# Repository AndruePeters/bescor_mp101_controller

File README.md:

# Bescor MP101 Controller

Solution to wirelessly control the Bescor MP101 pan and tilt camera motor.
User uses a PS4 controller to control the motor.

## Software Used
* [wiringPi](http://wiringpi.com/)
* [RF24](https://github.com/nRF24/RF24)
* [yaml-cpp](https://github.com/jbeder/yaml-cpp)
* [sfml](https://www.sfml-dev.org/)

## Devices Used
* [Arduino Uno](https://store.arduino.cc/usa/arduino-uno-rev3/) (although, I am using a cheap alternative from China.)
* [Raspberry Pi 3 Model B](https://www.raspberrypi.org/products/raspberry-pi-3-model-b/)
* [nRF24L01+ 2.4GHz](https://www.sparkfun.com/datasheets/Components/SMD/nRF24L01Pluss_Preliminary_Product_Specification_v1_0.pdf)
* [PS4 DualShock 4 Controller](https://www.playstation.com/en-us/explore/accessories/gaming-controllers/dualshock-4/)

# Installation

## Building
The following will actually compile and build the program natively on a Raspberry Pi. Please make sure that all dependencies are installed by running the install.sh script.

```
  (cd into the bescor_mp101_controller directory)
  cmake . -Bbuild
  cmake --build build
```

## Raspberry Pi
* **wiringPi** (dynamically linked since it is preinstalled)
  * wiringPi is installed by default. Follow [the instructions](http://wiringpi.com/download-and-install/) if you need to install it.
* **RF24** (statically linked)
  * `git clone https://github.com/nRF24/RF24`
  * `cd RF24/`
  * `./configure`
  * `sudo make install`
* **yaml-cpp** (statically inked)
  * Follow the instructions [here](https://github.com/jbeder/yaml-cpp).
* **sfml** (need to decide - probably statically linked)
  * If you have Debian then run `sudo apt-get install libsfml-dev`
  * Otherwise, follow the [official guide](https://www.sfml-dev.org/tutorials/2.5/start-linux.php) to manually install it. Version is 2.5 at the time of writing.

## YAML Configuration
Configuration settings for each node.
Example yaml file.
```yaml
camera_nodes:
  # this is the first came
  - channel: 1
    id: 1
    address: 1
    color: BLUE
    power_level: MAX
    data_rate: 250KBPS
    crc_length: DISABLED
    ir_proto: SONY
    zoom_in: 5
    zoom_out: 5
    focus_in: 5
    focus_out: 5

  # add following cameras here
```

#### Channel
Only channel 1 is supported at the moment

#### ID
Acceptable values: 1 - 255
0 is not allowed.

#### Address
Acceptable values: A1, A2, A3, A4, A5
At this point in time, I recommend only using A1

#### Color
Acceptable values:  OFF, BLUE, GREEN, CYAN, RED, MAGENTA, YELLOW, WHITE

#### Power Level
Acceptable values: MIN, LOW, HIGH, MAX

#### Data Rate
Acceptable values: 250KBPS, 1MBPS, 2MBPS
* The lower the speed the further the range. No reason in changing from 250KBPS for this application.

#### CRC Length
Acceptable values: DISABLED, CRC_8, CRC_16

#### IR Protocol
Acceptable values: SONY, NEC
* Hopefully, more will be supported in the future.

#### Zoom In, Zoom Out, Focus In, Focus Out
Any 32 bit number.

## Cross-compile
I created a basic [toolchain](https://github.com/AndruePeters/pi_toolchain) to cross compile for the Raspberry Pi.
The toolchain is simply the standard Raspberry Pi toolchain with precompiled libraries and headers I commonly use for my projects.
I'll write a better cross-compile description once I get the full thing back up.

# Controls
* L1 - cycles camera selection left
* R1 - cycles camera selection right
* L  - Controls the camera.
* R
  * Moving up and down zooms in and out
  * Moving left and right focuses in and out

# Packet Structure
## Motor Packets
`packet.packet_type = 0;`

`packet.payload_used = 3;`

`packet.payload[0] = speed`  This is an integer [0-255]

`packet.payload[1] = x_axis`. Values = {0, 1, 2}. 0 is off, 1 is left, 2 is right.

`packet.payloadp2] = y_axis`. Values = {0, 1, 2}. 0 is off, 1 is down, 2 is up.

## IR Packet
`packet.packet_type = 1;`

`packet.payload_used = 5;`

`packet.payload[0] = IR prot.`

`packet.payload[1 through 4]` is a 32 bit integer code with packet.payload[1] being the MSByte and packet.payload[4] LSByte

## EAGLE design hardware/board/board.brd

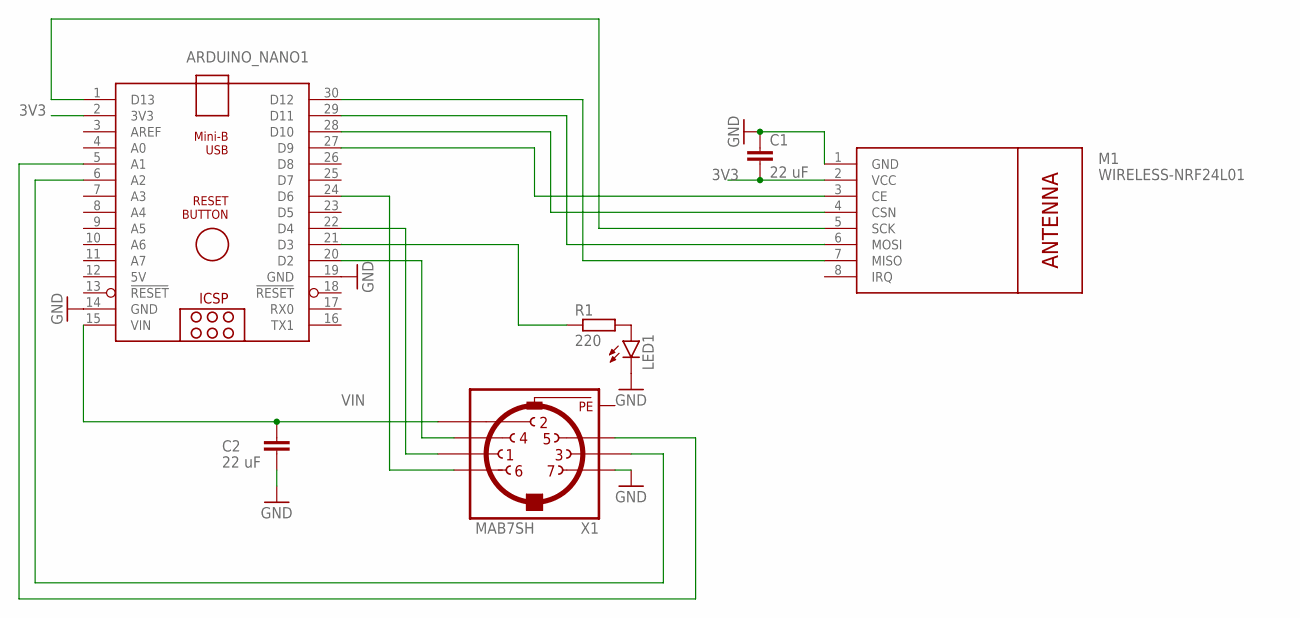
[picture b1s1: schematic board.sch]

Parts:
ARDUINO_NANO1: ARDUINO_NANO
C1, C2: 22 uF; C0805
LED1: LED5MM
M1: WIRELESS-NRF24L01
R1: 220; R0805
X1: MAB7SH

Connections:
3V3: ARDUINO_NANO1.2 (3V3), C1.2, M1.2 (VCC)
5V: ARDUINO_NANO1.12 (5V)
GND: ARDUINO_NANO1.14 (GND), ARDUINO_NANO1.19 (GND), C1.1, C2.2, LED1.K (C), M1.1 (GND), X1.7
unnamed: ARDUINO_NANO1.1 (D13), M1.5 (SCK)
unnamed: ARDUINO_NANO1.30 (D12), M1.7 (MISO)
unnamed: ARDUINO_NANO1.29 (D11), M1.6 (MOSI)
unnamed: ARDUINO_NANO1.28 (D10), M1.4 (CSN)
unnamed: ARDUINO_NANO1.27 (D9), M1.3 (CE)
unnamed: LED1.A, R1.2
unnamed: ARDUINO_NANO1.21 (D3), R1.1
unnamed: ARDUINO_NANO1.24 (D6), X1.6
unnamed: ARDUINO_NANO1.22 (D4), X1.1
unnamed: ARDUINO_NANO1.5 (A1), X1.5
unnamed: ARDUINO_NANO1.20 (D2), X1.4
unnamed: ARDUINO_NANO1.6 (A2), X1.3
PE: X1.PE, X1.PE@ (PE)
VIN: ARDUINO_NANO1.15 (VIN), C2.1, X1.2

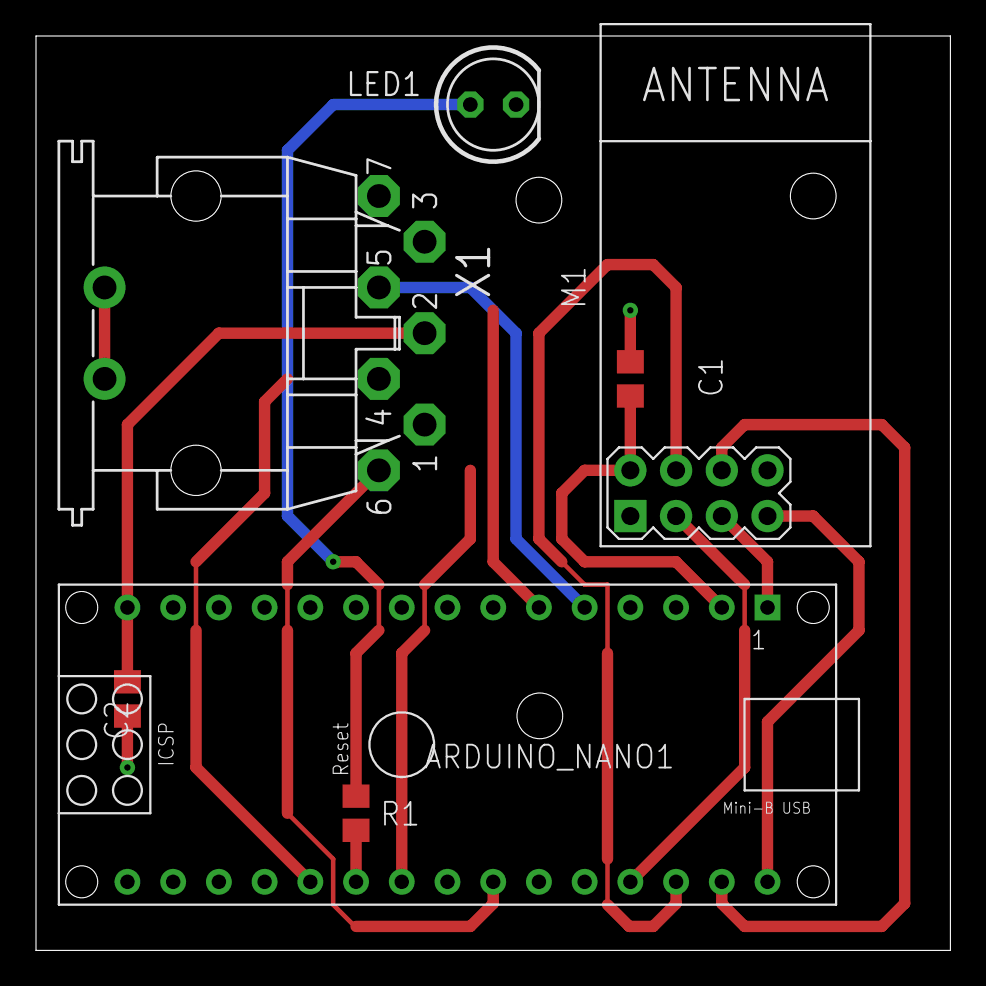
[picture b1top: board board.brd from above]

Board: 2 copper layers, 50.8 x 50.8 mm, 7 parts (0 on the bottom side), 16 nets.

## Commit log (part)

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2019-04-04 Added motor pinout
2019-04-04 init
2019-04-04 Test code for packet module
2019-04-04 Added basic packet structure and supporting methods.
2019-04-04 Layout for node
2019-04-05 Prototypes for node.
2019-04-05 Changed enum name scheme to end in *_e, and added defaults for init
2019-04-05 Added node_init
2019-04-05 Added ndoe_set_color
2019-04-05 Added node_get_color
2019-04-05 Added node_get/set_id
2019-04-05 Added todo
2019-04-05 Added node_set/get_power_level
2019-04-05 Added node_set/get_data_rate
2019-04-05 Formatting changes
2019-04-05 Added node_set/get_crc_length
2019-04-05 Added node_set/get_channel
2019-04-05 Added all rf related get/set functions
2019-04-07 Updated library linkage
2019-05-15 Added description for packet_set_payload_data()
2019-05-15 Fixed parameter typo in node_set_ir_port()
2019-05-15 Implemented node_init and also fixed typo in node_set_ir_prot()
2019-05-15 Makefile for packet_test.c
2019-05-15 Makefile for node_test.c
2019-05-15 Test file for node.h and node.c. Initially for compile checks
2019-05-15 Needed toolchain because of RF24 reliance
2019-05-15 Fixed typo with #include <RF24.h>
2019-05-15 Fixed all compile errors
2019-05-15 Fixed include issues
2019-05-15 Modified makefile for cflags
2019-05-15 edited
2019-05-15 To compile with toolchain
2019-05-17 Updated toolchain file and CMake
2019-05-17 Made sure wiringPi and RF24 are working nicely together
2019-05-17 Added yaml config example
2019-05-17 Attempted syntax highlighting for yaml config
2019-05-17 added description and fixed example
2019-05-17 Fixed typo in Color description
2019-05-17 Added adress options
2019-05-17 Test config file
2019-05-22 Ignores _build directories
2019-05-29 Init commit
2019-06-02 Added global instance
2019-06-02 Now includes packet folder
2019-06-02 Fixed error where it looked at wrong folder for node and packet
2019-06-02 Builds and transfrs to pi on network
2019-06-02 build file changes
2019-06-02 Upload and runs compiled file
2019-06-02 Calls wiringPi() and radio.begin() in proper order
2019-06-02 Changed RF24 include path
2019-06-15 Fixed Pi corruption and changed IP.
2019-06-15 Removed stdc++ and specific lib for RF24 in link
2019-06-15 Changed include to match native Pi installation
2019-06-15 Changed CXX and C compiler to use default installed compiler
2019-06-15 Changed RF24 include path to be consistent with native pi installation
2019-06-15 Tests main.cpp automatically on Pi
2019-06-15 Added more compile error/warning flags
2019-06-15 Changed address to listening_addr to better convey meaning
2019-06-15 Fixed ENDSSH issue
2019-06-15 Added helper methods to control radio
2019-06-15 Updated documentation
2019-06-15 Added send_packet() method
2019-06-15 Renamed address_e values to be compatible with Arduino IDE
2019-06-15 Initial Arduino commit
2019-06-21 Working wrapper for SFML
2019-06-21 Test for js.h
2019-06-21 Compiles and builds test program
2019-06-21 cMake config file for this test
2019-06-21 Controller mapping for PS4 and CMake
2019-06-21 Changes to test all controller settings
2019-06-24 Edited for new paths
2019-06-24 Fixed typo
2019-06-24 Moved file
2019-06-24 Added ncurses test dialog to see current state of controller
2019-06-24 Moved paths
2019-06-24 Fixed match_node_radio
2019-06-24 Uses Dual Shock 4 controller mappings
2019-06-24 Init. Controller mapping for DualShock 4 controller
2019-06-24 Added C++ cross compatible sleep method
2019-06-24 Added ability to monitor button state and see raw output.
2019-06-24 Added documentation
2019-06-24 Reformatted code, removed unnecessary btn_state
2019-06-24 Documentation updates
2019-06-24 Added tests
2019-06-25 Debugging flag added
2019-06-25 Working cyclic iterating
2019-06-25 Added curses screen with cycling nodes
2019-06-26 Working on controller mappings
2019-06-27 Function to normalize axis
2019-06-28 Functions to create IR and Motor packets
2019-06-28 Moved to joystick folder
2019-06-28 Moved to yaml_config/
2019-06-28 Moved to joystick/
2019-06-28 Include path reflects folder changes for js.h
2019-06-28 Changed link path for joystick
2019-06-28 Added proper const qualifications to functions
2019-06-28 Added getNormAxis()
2019-06-28 removed #include <bitset>
2019-06-28 Switched to using JS_State::getNormAxis()
2019-06-28 Links to libyaml-cpp
2019-06-28 Added code to read yaml config files
2019-06-28 Example configuration file
2019-06-28 Changed IDs and colors
2019-06-28 Loads information from yaml config. Weird issue with .as<uint8_t>, so changed to .as<unsigned> for getting id
2019-06-28 Added methods to control motor
2019-06-30 Links with ncurses
2019-06-30 Added methods used in tests/non_pi_test
2019-07-01 revamped
2019-07-01 Dependency installer script
2019-07-03 Changed definition of process_input
2019-07-03 Added getAxisMagnitude()
2019-07-03 Cycles nodes and sends motor packet
2019-07-03 Single parameter getAxisMagnitude() implemented
2019-07-03 Creates and sends IR packet
2019-07-03 Added load_config()
2019-07-03 Prototypes for converting string to data type from config.yaml
2019-07-03 Changed description[50] in struct node_prop to std::string
2019-07-03 Began reading config values
2019-07-05 Added str_to_clr
2019-07-05 Added str_to_pwr
2019-07-05 Added str_to_datarate
2019-07-05 Added str_to_crclen
2019-07-05 Added str_to_irprot
2019-07-05 Removed ir protocol define statements and updated node.h ir_prot_e
2019-07-05 Updated ir_prot_e to match IRLIB2
2019-07-05 Removed -Werror
2019-07-05 str_to_irprot() now return ir_prot_e
2019-07-05 libyaml-cpp now added from package maintainer
2019-07-05 Outputs include and link directories.
2019-07-05 Fixed bugs
2019-07-05 Commented lines out to make it work.....
2019-07-05 Added #include <string>
2019-07-05 Removed unneeded files
2019-07-05 Changed definition of load_config()
2019-07-05 Uploads config.yaml
2019-07-05 Added more settings
2019-07-05 Loads node
2019-07-06 Static libyaml-cpp library because package maintainer's shared version did not work for whatever reason over cross compilation. Compiled this library myself
2019-07-06 Added current directory to link_directories
2019-07-06 Added more examples
2019-07-06 Fixd load_config()
2019-07-06 Added debug flag.
2019-07-06 Print node
2019-07-06 pritn_curr_node()
2019-07-06 waitUntilConnected() is now not const and sleeps for 15 ms every loop
2019-07-06 If joystick not connected, then wait's for input. Replaced sleep with std::this_thread::sleep_for()
2019-07-06 Began main process and fixed up some documentation
2019-07-06 Removed commented out code
2019-07-06 in node_prop, description made char[50] instead of std::string
2019-07-06 Added all IR protocols
2019-07-06 Test logic for combining uint8_t components into uint32_t code
2019-07-06 Added libraries to make it easier to install for others.
2019-07-06 Added init_display() and display_status()
2019-07-06 Removed some debug code and implemented init_display() and display_status()
2019-07-06 Debug print statements now print to ncurses
2019-07-06 Added some debug statements in process_input() to verify packet is correct
2019-09-23 Gracefully handles Ctrl-C and also fixed bug where it wouldn't communicate
2019-09-23 Doesn't autorun
2019-09-23 Uses g++-8
2019-10-28 Working on adding motor and IR funcitnality
2019-10-28 node files because stupid Arduino IDE can't go up folders
2019-10-28 packet fiels becasue stupid Arduino IDE can't go up folders
2019-10-28 function prototypes. will rename
2019-10-29 Added input_packet and began init_rf24()
2019-10-29 Changed packet type setting to use enum.
2019-10-29 Process packet functions now accept a packet instead of operating on a global
2019-10-29 Removed convoluted fsm design; implemented loop(); implemented process_packet, process_ir_packet(), init_rf24()
2019-10-30 Added erase_packet() and includes for node and packet
2019-10-30 Added IR_LIB includes, fixed IRsend typo, implemented checking input_packet.id, erase_packet(), init_pins(), removed commented-out code, fixed motor_pin_config in config_motor_pins(), erase_packet() 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
2019-10-30 Removed old platformio related files
2019-11-01 Removed ir from led_pin_config, and added function prototypes for turn_on_leds()
2019-11-01 Added AceButton, static_cast in process_ir_packet, added rgb color functionality
2019-11-03 Many changes including adding support to change the arduino node id
2019-11-11 Fixed button bug and changed order colors
2019-11-16 Added installation for ncurses
2019-11-16 Cleans build direcotry
2019-11-16 Switched LED pins and button changes Arduino Id
2019-11-16 Fixed sudo -u
2019-11-16 Updated typo
2019-11-16 Fixed bug where correct packet id wasn't being sent.
2019-11-16 Changed motor delay
2019-11-16 Fixed id being sent over payload
2019-11-17 Remove match_node_radio which was cuasing the radio not to work if changing nodes.
2019-11-17 base 0 indexing
2019-11-17 Good files
2019-11-29 Changed thread sleep
2019-11-30 Added ir_bit_width
2019-11-30 Changed ir_bit_width to be a 32 bit field
2019-11-30 static_cast in create_ir_packet
2019-11-30 Fixed type signatures
2019-11-30 Sketch now knowledgeable about number of bits in IR protocol
2019-11-30 Fixed return type
2019-11-30 Bug fixes
2019-11-30 Format changes
2019-11-30 Formatting differences
2019-11-30 Removed debug statement
2019-11-30 Pi now has RGB indicator
2019-11-30 Offsets for controller sensitivity
2019-11-30 Changed alg
2019-11-30 Fixed bug
2019-11-30 User must pass in path to config file
2019-11-30 O3 optimization
2019-11-30 Removed optimization because I can't test for this first release
2019-12-01 Try to shutoff
2019-12-01 blink led when joystick not connected
2019-12-01 blink no controller
2019-12-01 Commented out expeirmental feature
2019-12-01 debug
2019-12-01 cout
2019-12-01 Fixed bug causing controller to not shutdown
2019-12-04 Test travis upload for packages
2019-12-04 add armhf architecture to apt
2019-12-04 arch flag
2019-12-04 Changed arch
2019-12-05 Added wiringPi from conan and install for RF24 library
2019-12-05 Rudementary python support. Should change in future
2019-12-05 use pip3
2019-12-05 Might as well us bionic if I want newer packages
2019-12-05 install conan binary
2019-12-05 Revert "install conan binary"
    This reverts commit ffd2f40ad10019e5b6528553ab99b56185065310.
2019-12-05 Installs python3-dev
2019-12-05 Nedded sudo
2019-12-05 It told me to add -H to sudo
2019-12-05 Working on wiringPi
2019-12-05 removed conan user
2019-12-05 removed conan install because of issues
2019-12-05 Removed armhf architecture because it didn't work
2019-12-05 Fixed gcc and g++ install issues
2019-12-05 Trying to run dpkg -add-architecture armhf before addons runs
2019-12-05 Fixed permissions error
2019-12-05 added universe repo
2019-12-05 try to fix
2019-12-05 tryin to fix
2019-12-05 will this work?
2019-12-05 trying to print out managed sources file
2019-12-05 print statemetns
2019-12-05 added arch back
2019-12-05 sed line
2019-12-05 working on conant support
2019-12-05 trying to get wiringPi
2019-12-12 Should fix camera stutter when IR commands and motor commands are sent by reducing packets sent
2019-12-13 fix compile issue
2019-12-13 fixed compile
2019-12-13 Implemented comparison operator
2019-12-13 Fixed operator
2019-12-13 Fixed operator!=
2019-12-13 fix mismatch comment
2019-12-18 init pcb files
2019-12-18 Connected radio
2020-11-06 changed project structure
2020-11-06 reformatted
2020-11-06 RF24 v1.3.9
2021-02-08 Updated 'add_executable()'
2021-02-08 added cmake build instructions
2021-02-11 removed acebutton library
2021-04-11 circuit template
2021-04-12 ignore eagle files
2021-04-12 added schematic and board files
2021-04-20 added arduino hardware
2021-04-21 value update
2021-05-29 connected 3V3 radio line to the aruino nano
2021-05-29 Fixed radio pins to be 9 and 10 that reflect the PCB board
2021-05-29 conan support with FMT and SPDLOG
2021-05-29 re-added ncurses support
2021-05-29 removed ncurses
2022-01-09 Update main.cpp
    Commented out config properties that aren't currently in use.
2022-05-24 fixed circuitboard
2022-06-24 ignore .vscode
2022-06-24 space out stop commands in case stop command was not received

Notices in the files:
parts and their libraries:
nrf24l01: Released under the Creative Commons Attribution 4.0 International License: http://creativecommons.org/licenses/by/4.0
